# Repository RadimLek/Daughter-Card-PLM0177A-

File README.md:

# Daughter-Card-PLM0177A-
BFAN9673 Evaluation Board 
NOT COMPLETE

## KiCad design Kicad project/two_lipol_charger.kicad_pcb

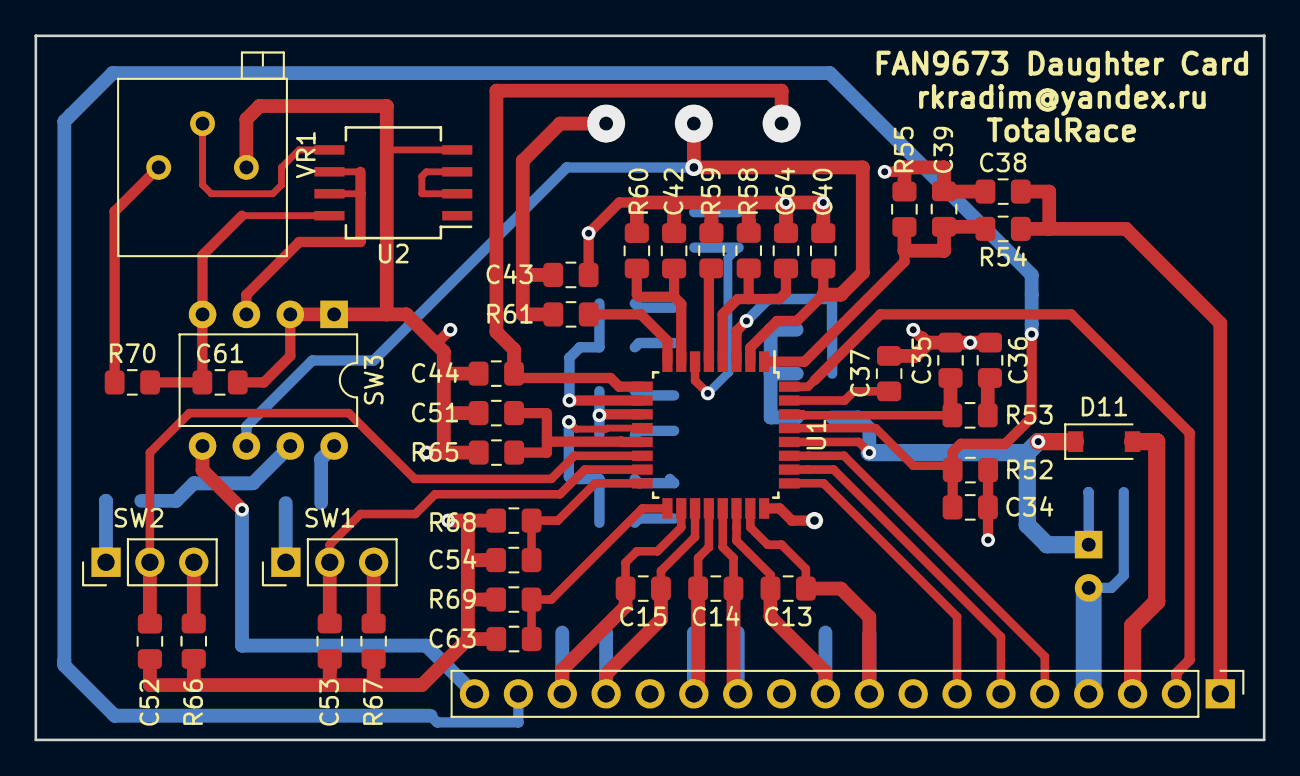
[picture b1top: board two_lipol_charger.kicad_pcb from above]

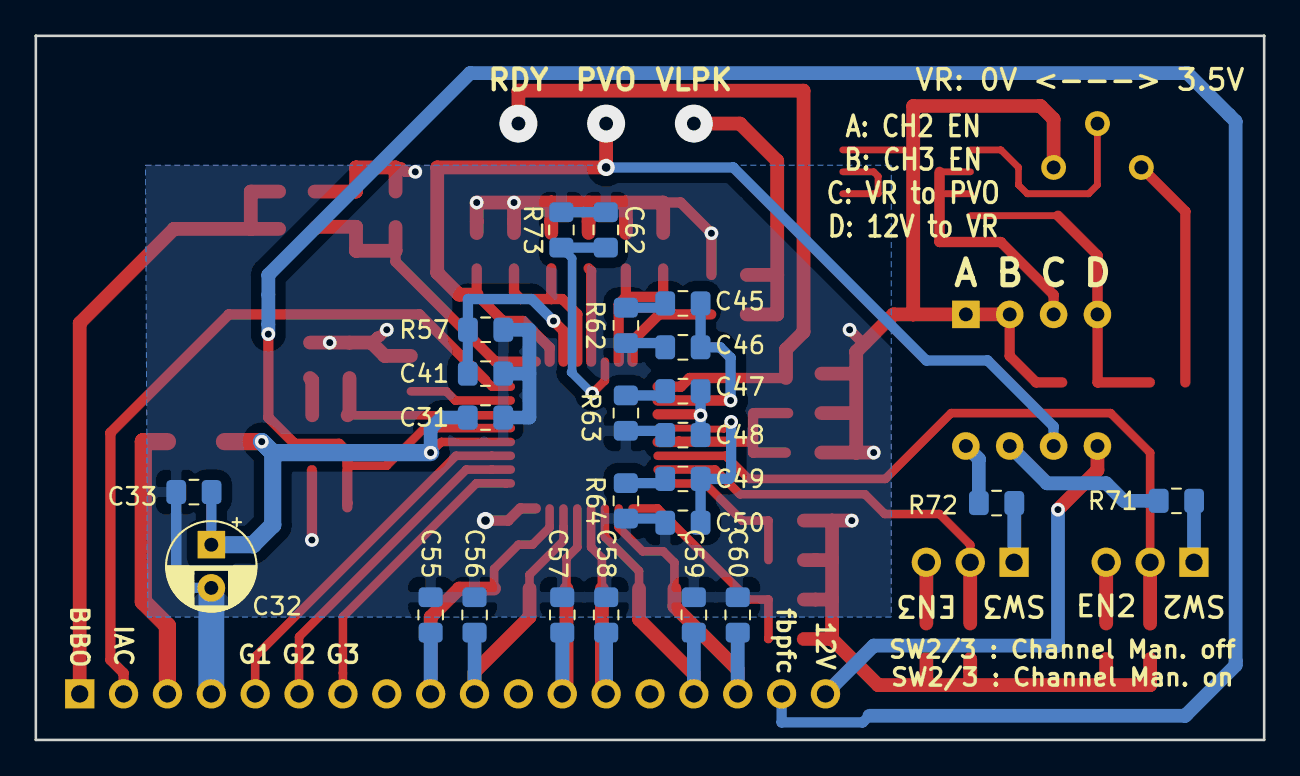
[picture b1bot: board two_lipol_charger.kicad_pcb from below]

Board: 2 copper layers, 71.1 x 40.8 mm, 66 parts (24 on the bottom side), 51 nets.

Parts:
C13, C14, C15: 1nF; C_0805_2012Metric_Pad1.15x1.40mm_HandSolder
C31, C33, C43, C44, C61: 0.1uF; C_0805_2012Metric_Pad1.15x1.40mm_HandSolder
C32: 10uF; CP_Radial_D5.0mm_P2.50mm
C34: 470pF; C_0805_2012Metric_Pad1.15x1.40mm_HandSolder
C35, C40, C41, C42, C51, C54: 0.01uF; C_0805_2012Metric_Pad1.15x1.40mm_HandSolder
C36, C37, C39, C52, C53: 0.47uF; C_0805_2012Metric_Pad1.15x1.40mm_HandSolder
C38: 0.047uF; C_0805_2012Metric_Pad1.15x1.40mm_HandSolder
C45, C47, C49: 1.2nF; C_0805_2012Metric_Pad1.15x1.40mm_HandSolder
C46, C48, C50, C62: 100pF; C_0805_2012Metric_Pad1.15x1.40mm_HandSolder
C55, C56, C57, C58, C59, C60: 2.2nF; C_0805_2012Metric_Pad1.15x1.40mm_HandSolder
C63, C64: 330pF; C_0805_2012Metric_Pad1.15x1.40mm_HandSolder
D11: 1n4148; D_SOD-123
J1: Conn_01x18; PinHeader_1x18_P2.54mm_Vertical
R52: 23.7k; R_0805_2012Metric_Pad1.15x1.40mm_HandSolder
R53: 75k; R_0805_2012Metric_Pad1.15x1.40mm_HandSolder
R54: 200k; R_0805_2012Metric_Pad1.15x1.40mm_HandSolder
R55: 16.2k; R_0805_2012Metric_Pad1.15x1.40mm_HandSolder
R57: 27k; R_0805_2012Metric_Pad1.15x1.40mm_HandSolder
R58: 38.3k; R_0805_2012Metric_Pad1.15x1.40mm_HandSolder
R59: 20k; R_0805_2012Metric_Pad1.15x1.40mm_HandSolder
R60: 10k; R_0805_2012Metric_Pad1.15x1.40mm_HandSolder
R61: 4.7k; R_0805_2012Metric_Pad1.15x1.40mm_HandSolder
R62, R63, R64: 17.4k; R_0805_2012Metric_Pad1.15x1.40mm_HandSolder
R65, R71, R72: 0; R_0805_2012Metric_Pad1.15x1.40mm_HandSolder
R66, R67, R70: 47k; R_0805_2012Metric_Pad1.15x1.40mm_HandSolder
R68: 470k; R_0805_2012Metric_Pad1.15x1.40mm_HandSolder
R69: 33k; R_0805_2012Metric_Pad1.15x1.40mm_HandSolder
R73: 12.1k; R_0805_2012Metric_Pad1.15x1.40mm_HandSolder
SW1, SW2: SW_DPDT_x2; PinHeader_1x03_P2.54mm_Vertical
SW3: SW_DIP_x04; DIP-8_W7.62mm
U1: FAN9673; LQFP-32_7x7mm_P0.8mm
U2: LM358D; SO-8_5.3x6.2mm_P1.27mm
VR1: 20k; Potentiometer_Bourns_3296P_Horizontal

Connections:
12V: J1.18, SW3.5
15V: C31.2, C32.2, C33.1, D11.1, U1.28
BIBO: C38.2, J1.1, R54.1
CS1+: C13.1, C55.1, J1.9, U1.23
CS1-: C13.2, C56.1, J1.10, U1.22
CS2+: C14.1, C57.1, J1.12, U1.21
CS2-: C14.2, C58.1, J1.13, U1.20
CS3+: C15.1, C59.1, J1.15, U1.19
CS3-: C15.2, C60.1, J1.16, U1.18
CVM2: C52.1, SW2.2, U1.14
CVM3: C53.1, SW1.2, U1.15
FBPFC: C34.2, J1.17, R52.1, U1.29
GND: C31.1, C32.1, C33.2, C34.1, C35.1, C36.1, C37.1, C38.1, C39.1, C40.1, C41.1, C42.1, C43.2, C44.1, C46.1, C48.1, C50.1, C51.1, C52.2, C53.2, C54.1, C55.2, C56.2, C57.2, C58.2, C59.2, C60.2, C61.2, C62.1, C63.2, C64.1, J1.4, R52.2, R55.2, R57.2, R58.2, R59.2, R60.2, R62.2, R63.2, R64.2, R65.2, R66.1, R67.1, R68.2, R69.1, R73.2, SW3.1, SW3.2, U1.24, U2.4, VR1.1
IAC: J1.2, U1.32
unnamed: C35.2, R53.1, U1.30
unnamed: C36.2, R53.2
unnamed: C37.2, U1.31
unnamed: C39.2, R54.2, R55.1, U1.1
unnamed: C41.2, R57.1, U1.3
unnamed: C42.2, R60.1, U1.7
unnamed: C45.1, R62.1
unnamed: C45.2, C46.2, U1.10
unnamed: C47.1, R63.1
unnamed: C47.2, C48.2, U1.11
unnamed: C49.1, R64.1
unnamed: C49.2, C50.2, U1.12
unnamed: C51.2, R65.1, U1.13
unnamed: C54.2, R68.1, U1.16
unnamed: C61.1, R70.2, SW3.4, U2.8
unnamed: C62.2, R73.1, U1.6
unnamed: C63.1, R69.2, U1.17
unnamed: C64.2, R58.1, U1.4
unnamed: R59.1, U1.5
unnamed: R61.1, U1.8
unnamed: R66.2, SW2.3
unnamed: R67.2, SW1.3
unnamed: R70.1, VR1.3
unnamed: R71.1, SW3.7
unnamed: R71.2, SW2.1
unnamed: R72.1, SW3.8
unnamed: R72.2, SW1.1
unnamed: SW3.3, U2.6, U2.7
unnamed: U2.2, U2.3
unnamed: U2.5, VR1.2
OPFC1: J1.5, U1.27
OPFC2: J1.6, U1.26
OPFC3: J1.7, U1.25
PVO: C40.2, SW3.6, U1.2
RDY: C44.2, U1.9
VDD: D11.2, J1.3
VLPK: C43.1, R61.2

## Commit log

2019-01-14 Version 1.0
